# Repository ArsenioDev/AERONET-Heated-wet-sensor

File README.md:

# AERONET-Heated-wet-sensor

## Heated Wet Sensor for the NASA AERONET program

Designed as part of USNA-to-NASA internship by Victor Zimmerman. 

### Description

A PCB designed to cure NASA AERONET robots suffering from dew induced crepuscular narcolepsy (instruments remaining in standby due to dew on wet sensor). The PCB is connected to temperature sensors, CIMEL control box and a heated wet sensor, in order to determine if the wet sensor is at risk of dew condensation. If so, turns on heater to prevent dew condensation. Determines dew risk by calculating dew point at BME280(atmospheric DP) and compares it to dew point calculated by temperature sensor underneath heated wet sensor(Sensor DP). Heats wet sensor until sensor DP is higher than atmospheric DP. Formula used to calculate dew point: 

Is mostly a "plug-and-play" design; does not need any programming or input from operator beyond initial code load. Runs on 12V and minimum 1.5A AC power supply (1.2A of which is for the heater, I_Lim set by load driver).

#### Initial code load prerequisites/software dependencies
* Arduino IDE with [STM32Duino](https://github.com/stm32duino/Arduino_Core_STM32) BSP core added
* Include libraries: [BolderFlight BME280](https://github.com/bolderflight/bme280), [OneWire](https://github.com/PaulStoffregen/OneWire), and [DallasTemperature](https://github.com/milesburton/Arduino-Temperature-Control-Library)
* SWD (Serial Wire Debug) upload mechanism from list of uploads. 
* Core selected **Generic STM32F103C6**

### Progress
- [x] Attempted to use RX8130
- [x] failed to use RX8130 :(
- [x] Succesfully pivoted to DS3121
- [x] realized RTC was unneccesary 
- [x] finished code
- [x] finished spahgetti point to point (with italian falg colored wires)
- [ ] ~~failed test in temperature chamber~~
- [x] ~~give up creating dew condensation after a PHD told us it would not work~~
- [x] Meanwhile, forced dew condensation in temperature chamber
- [x] Defined schematic of PCB with teensy stand in
- [x] replaced teensy with STM32F103
- [x] Finished schematic
- [x] routed PCB
- [x] Fine Tuned
- [x] Swagged out silkscreen
- [x] issued production order
- [x] finished progress list
- [ ] finished README and documentat...zzz

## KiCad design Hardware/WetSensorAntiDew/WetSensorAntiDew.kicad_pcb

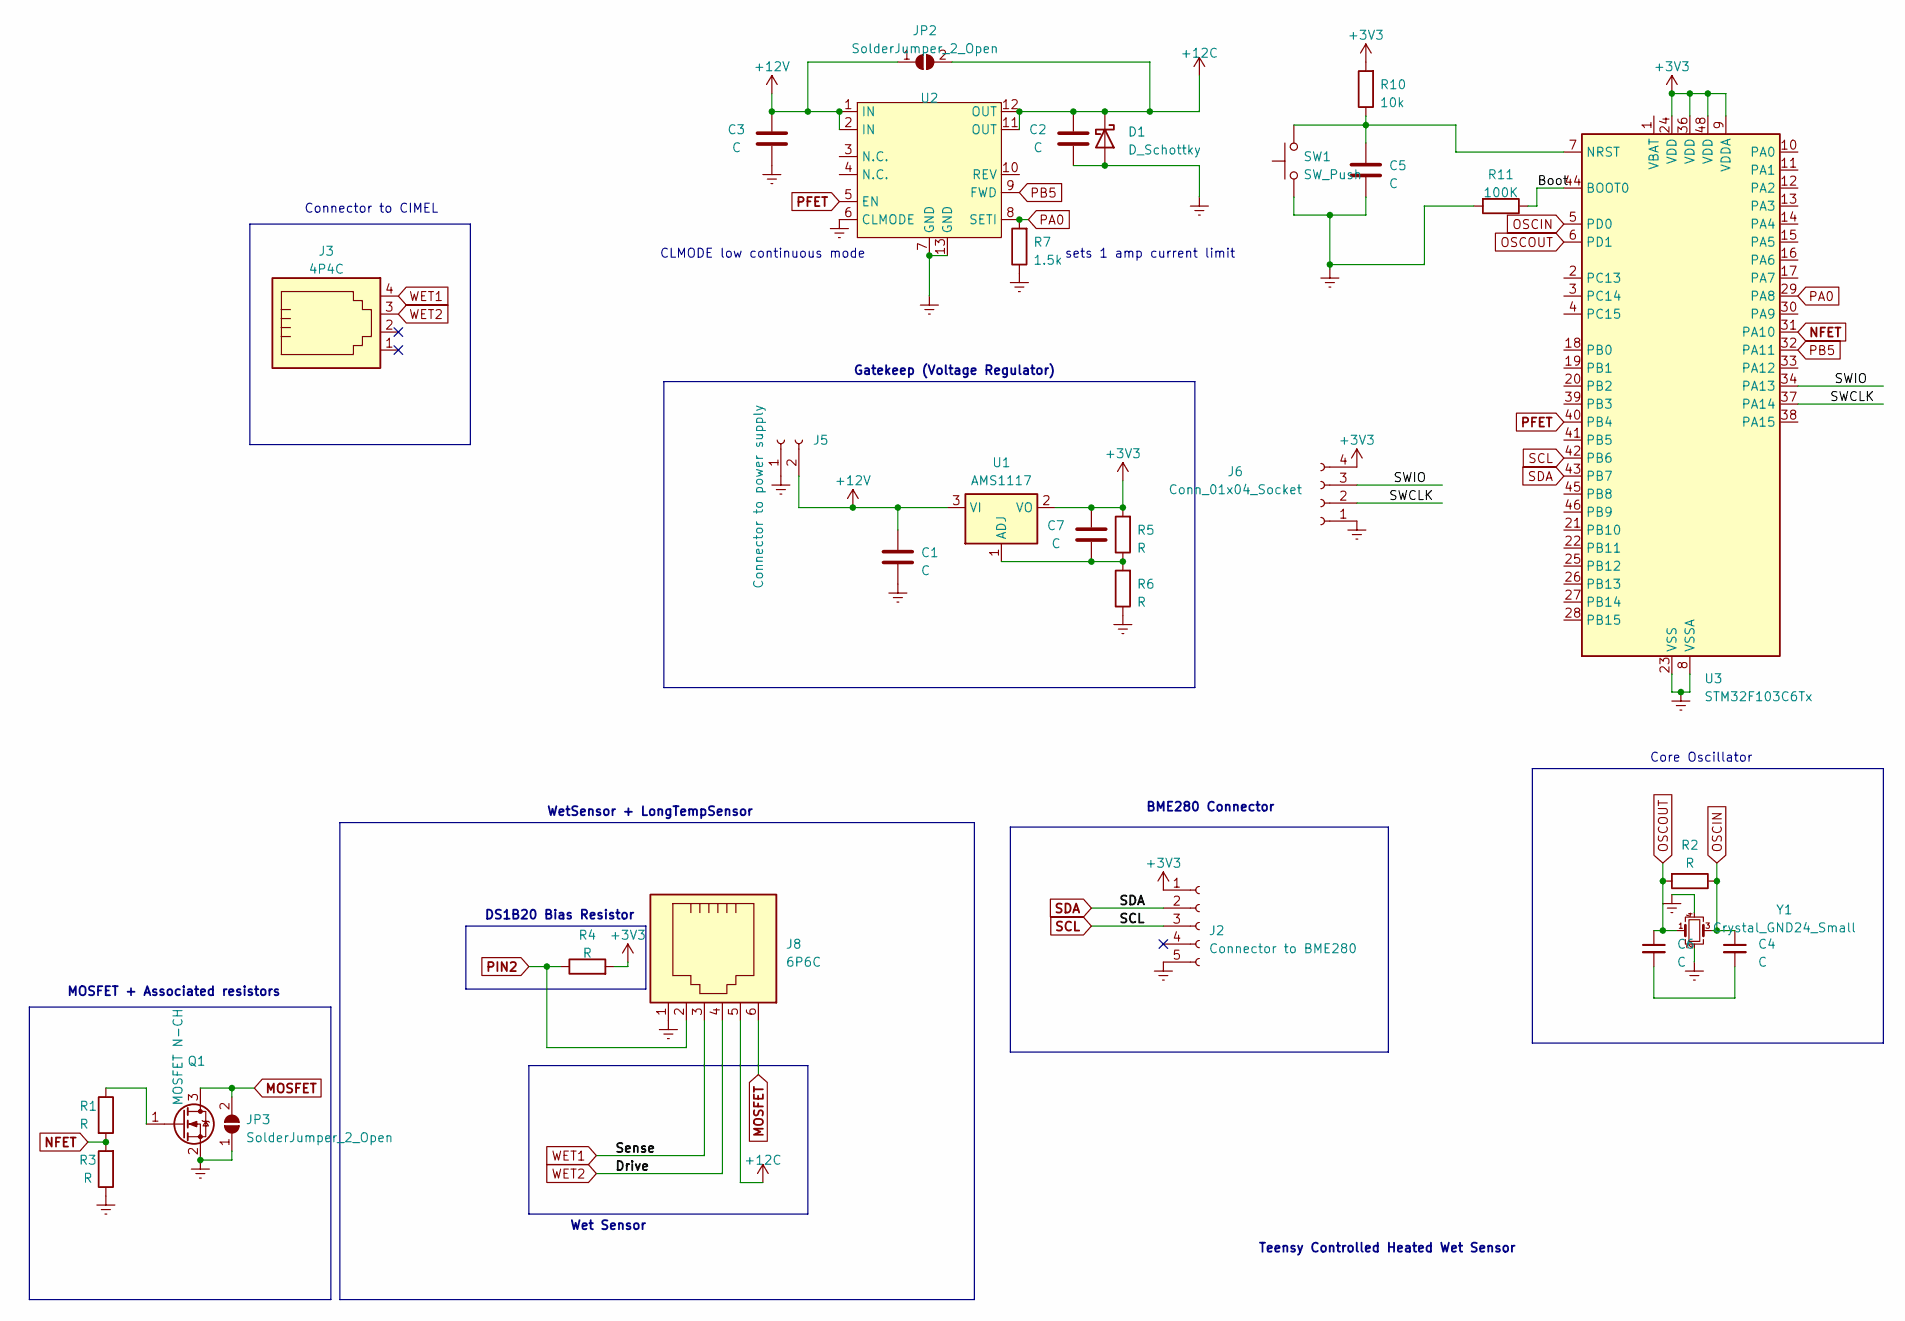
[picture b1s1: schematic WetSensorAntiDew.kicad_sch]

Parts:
C1, C2, C3, C4, C5, C6, C7: C; C_0603_1608Metric_Pad1.08x0.95mm_HandSolder
D1: D_Schottky; D_SOD-323
J2: Connector to BME280; PinSocket_1x05_P2.54mm_Horizontal
J3: 4P4C; BEL_SS-6444-NF
J5: Connector to power supply; PhoenixContact_MC_1,5_2-G-3.81_1x02_P3.81mm_Horizontal
J6: Conn_01x04_Socket; FanPinHeader_1x04_P2.54mm_Vertical
J8: 6P6C; RJ12_Amphenol_54601
JP2, JP3: SolderJumper_2_Open; SolderJumper-2_P1.3mm_Open_Pad1.0x1.5mm
Q1: MOSFET N-CH; SOT-23
R1, R2, R3, R4, R5, R6: R; R_0603_1608Metric_Pad0.98x0.95mm_HandSolder
R7: 1.5k; R_0603_1608Metric_Pad0.98x0.95mm_HandSolder
R10: 10k; R_0603_1608Metric_Pad0.98x0.95mm_HandSolder
R11: 100K; R_0603_1608Metric_Pad0.98x0.95mm_HandSolder
SW1: SW_Push; 228EJVAYFR
U1: AMS1117; SOT-223-3_TabPin2
U2: DFN-12-1EP_3x3mm_P0.5mm_EP1.6x2.5mm_ThermalVias
U3: STM32F103C6Tx; LQFP-48_7x7mm_P0.5mm
Y1: Crystal_GND24_Small; Crystal_SMD_3225-4Pin_3.2x2.5mm

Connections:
+3V3: C7.1, J2.1, J6.4, R4.2, R5.2, R10.2, U1.2 (VO), U3.9 (VDDA), U3.24 (VDD), U3.36 (VDD), U3.48 (VDD)
+12C: C2.1, D1.1 (K), J8.5, JP2.2 (B), U2.11 (OUT), U2.12 (OUT)
+12V: C1.1, C3.1, J5.2, JP2.1 (A), U1.3 (VI), U2.1 (IN), U2.2 (IN)
/Boot: R11.1, U3.44 (BOOT0)
/SWCLK: J6.2, U3.37 (PA14)
/SWIO: J6.3, U3.34 (PA13)
Earth: C1.2, C2.2, C3.2, C5.2, D1.2 (A), J2.5, J5.1, J6.1, J8.1, JP3.1 (A), Q1.2 (S), R3.1, R6.1, R7.1, R11.2, SW1.1, U2.6 (CLMODE), U2.7 (GND), U2.13 (GND), U3.8 (VSSA), U3.23 (VSS), U3.35 (VSS), U3.47 (VSS), Y1.2, Y1.4; also elsewhere on the board
MOSFET: J8.6, JP3.2 (B), Q1.3 (D)
NFET: R1.2, R3.2, U3.31 (PA10)
unnamed: C4.2, C6.2
unnamed: Q1.1 (G), R1.1
unnamed: C7.2, R5.1, R6.2, U1.1 (ADJ)
unnamed 12: C5.1, R10.1, SW1.2, U3.7 (NRST); also elsewhere on the board
OSCIN: C4.1, R2.1, U3.5 (PD0), Y1.3
OSCOUT: C6.1, R2.2, U3.6 (PD1), Y1.1
PA0: R7.2, U2.8 (SETI), U3.29 (PA8)
PB5: U2.9 (FWD), U3.32 (PA11)
PFET: U2.5 (EN), U3.40 (PB4)
PIN2: J8.2, R4.1
SCL: J2.3, U3.42 (PB6)
SDA: J2.2, U3.43 (PB7)
WET1: J3.4, J8.3
WET2: J3.3, J8.4

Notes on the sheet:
DS1B20 Bias Resistor
CLMODE low continuous mode
Wet Sensor
MOSFET + Associated resistors
BME280 Connector
Connector to CIMEL
WetSensor + LongTempSensor
Teensy Controlled Heated Wet Sensor
sets 1 amp current limit
Core Oscillator
Gatekeep (Voltage Regulator)

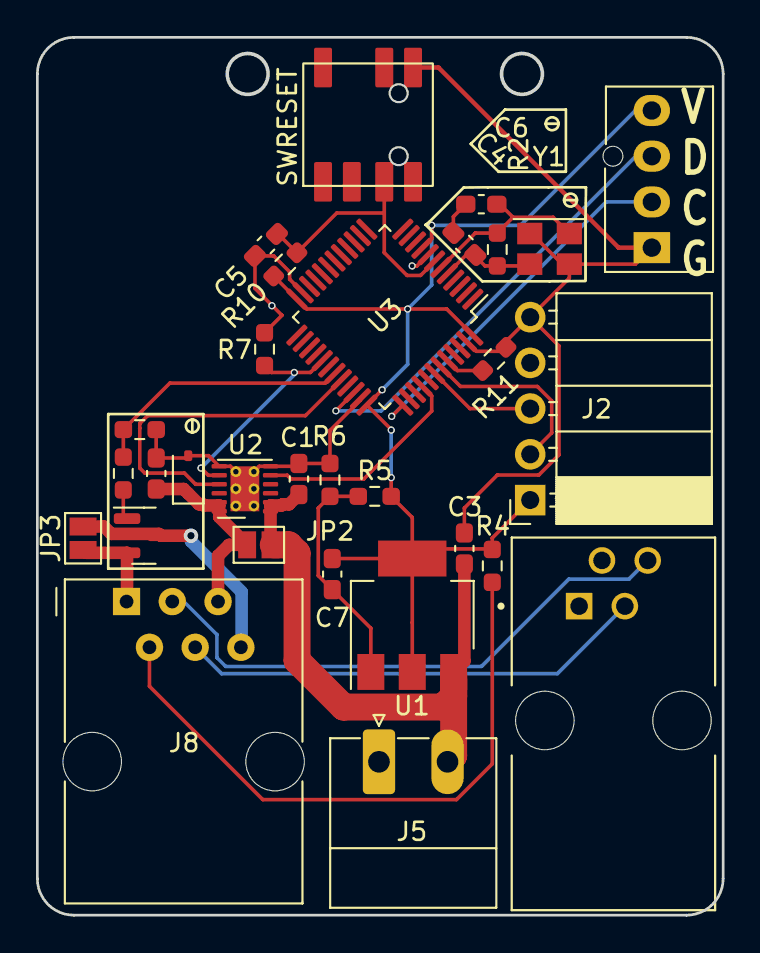
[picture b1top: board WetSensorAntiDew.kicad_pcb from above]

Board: 2 copper layers, 38.1 x 48.7 mm, 30 parts (0 on the bottom side), 23 nets.

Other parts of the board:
SWRESET: SW_Push; 228EJVAYFR

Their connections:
Earth: SWRESET.1; also elsewhere on the board
unnamed 12: SWRESET.2; also elsewhere on the board

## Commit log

2023-06-02 Initial code ingress
2023-06-05 Modifications
2023-06-07 initial board setup
2023-06-07 First schematic of HeatedWetSensorPCB
2023-06-07 Added Gatekeep
2023-06-07 added connector to gatekeep for power supply
2023-06-07 added footprints and properly spaced teensy connectors
2023-06-07 finished Pcb layout
2023-06-07 end of day commit on JUN 7
2023-06-08 upstream last changes
2023-06-08 WIP new voltage regulator
2023-06-08 add file for footprint of 4p4c
2023-06-08 added custom stm32 core
2023-06-08 Updates to board
2023-06-08 More progress
2023-06-09 Final* PCB design
2023-06-09 small edits to DRC Check pass
2023-06-09 edited switch and programming pins connections
2023-06-09 added USNA logo
2023-06-09 shrunk anchors aweigh
2023-06-09 USNA emblem tweaks
2023-06-09 Added Semper Supra :)
2023-06-09 Finalized silkscreen
2023-06-09 Tuned pinouts, corrected N/P switches
2023-06-09 Reset silk, corrected prog header
2023-06-09 Final design review pre-fab tuning
2023-06-09 added images for read me
2023-06-09 Update README.md
    added ray tracing images
2023-06-09 added progress report to README.md
2023-06-12 Added images to IMG directory
2023-06-12 added image to README.md
2023-06-12 removed image README.md
2023-06-12 added description and software dependencies section to README.md
2023-06-15 Updated readme and added images of holder prototyping
2023-06-16 updated heated wet sensor holder to include nubbin for heat shrink
2023-06-16 shortened sensor holder
2023-06-21 added a 3D printed box for pcb
2023-06-21 Added iBOM
2023-06-23 Closeout updates to bring to parity with PCB
